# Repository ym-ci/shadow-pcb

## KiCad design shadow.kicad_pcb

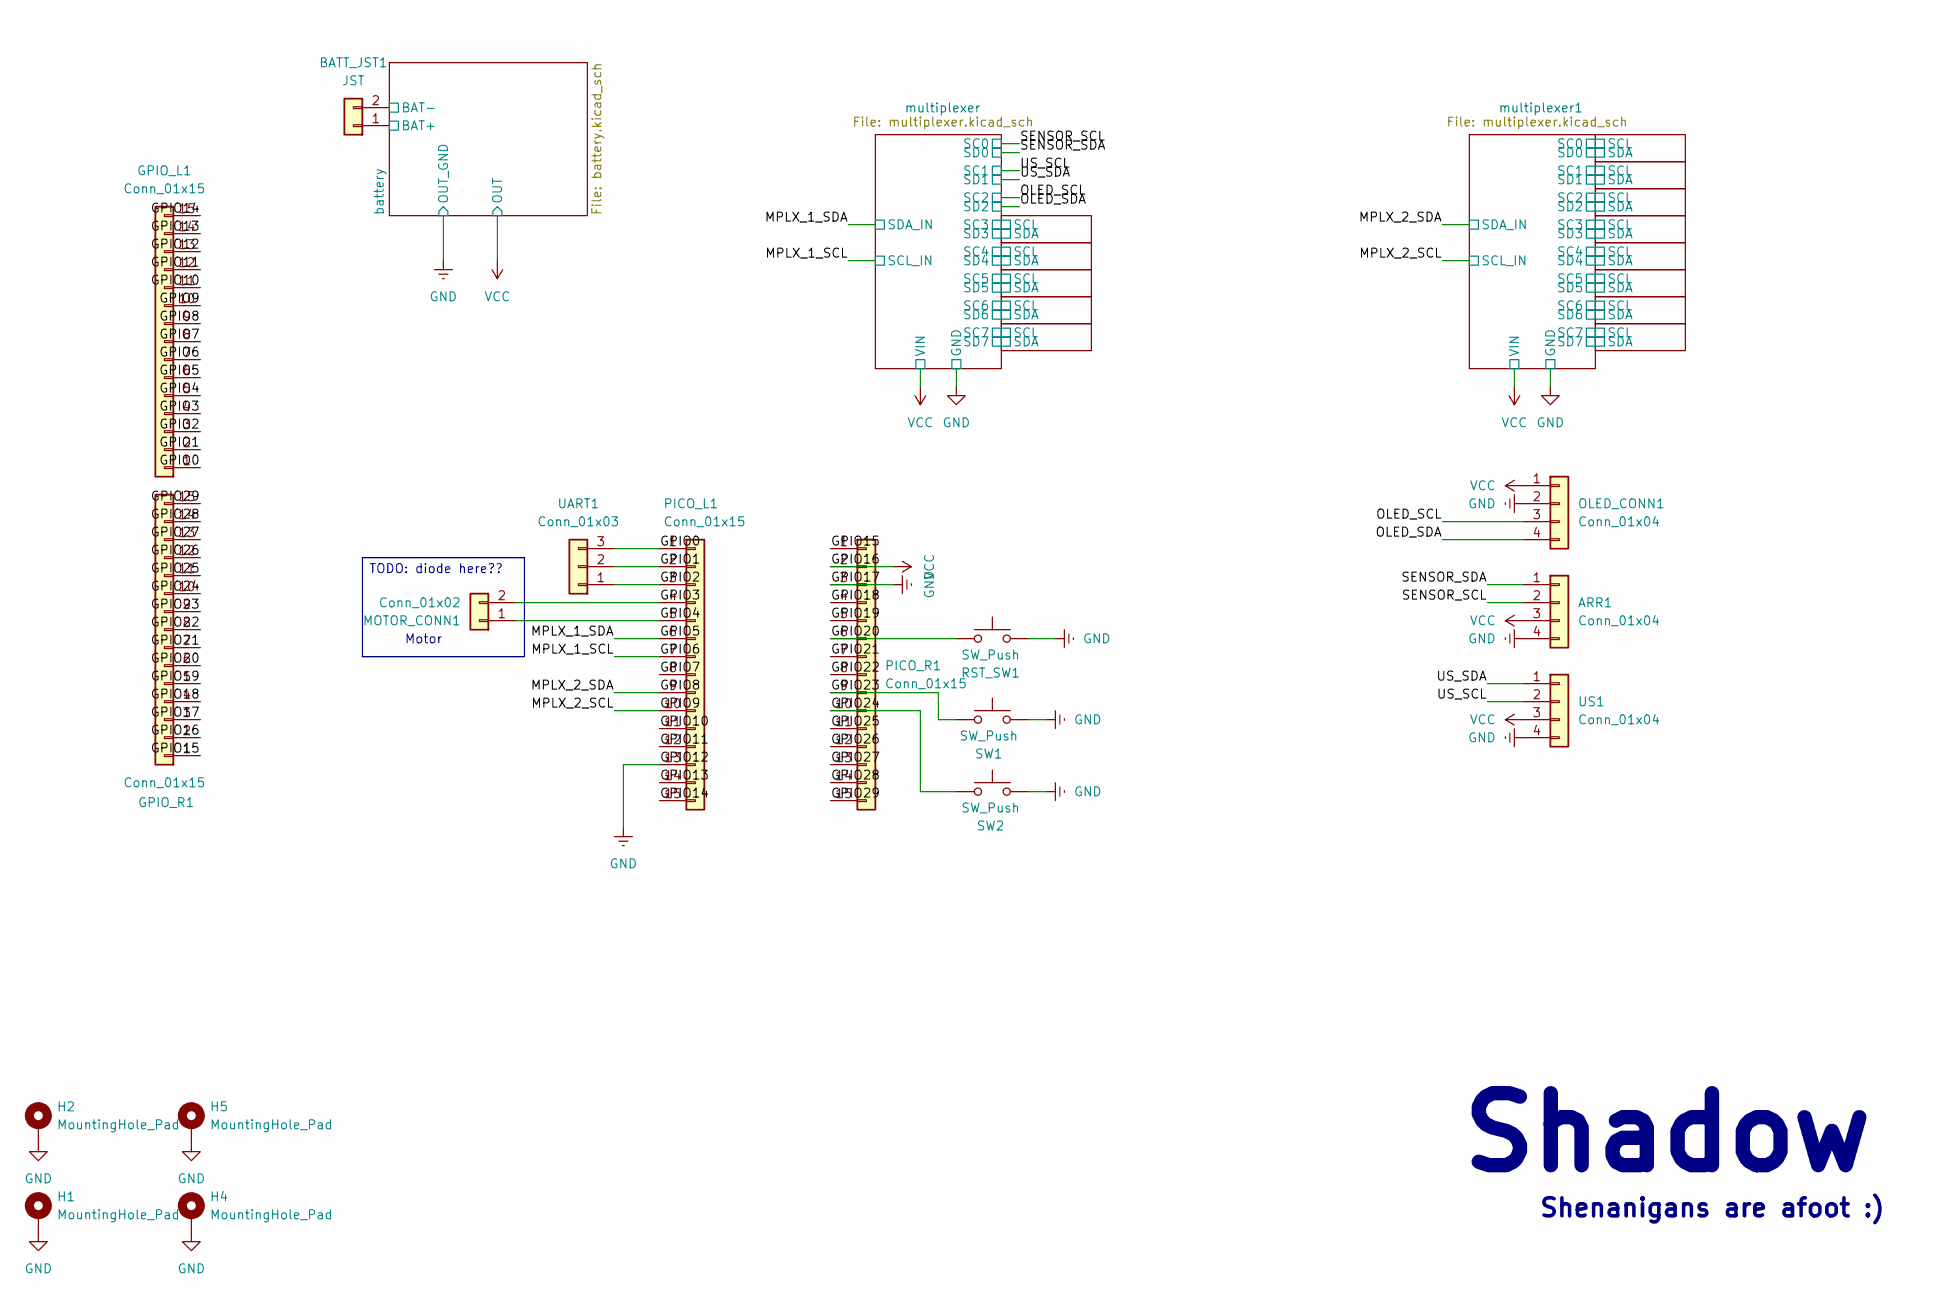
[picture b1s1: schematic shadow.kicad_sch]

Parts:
ARR1: Conn_01x04; PinSocket_1x04_P2.54mm_Vertical
BATT_JST1: JST; JST_XH_B2B-XH-A_1x02_P2.50mm_Vertical
GPIO_L1: Conn_01x15; PinSocket_1x15_P2.54mm_Vertical
GPIO_R1: Conn_01x15; PinSocket_1x15_P2.54mm_Vertical
H1, H2, H4, H5: MountingHole_Pad; MountingHole_4.3mm_M4_DIN965_Pad
MOTOR_CONN1: Conn_01x02; PinSocket_1x02_P2.54mm_Vertical
OLED_CONN1: Conn_01x04; PinSocket_1x04_P2.54mm_Vertical
PICO_L1: Conn_01x15; PinSocket_1x15_P2.54mm_Vertical
PICO_R1: Conn_01x15; PinSocket_1x15_P2.54mm_Vertical
RST_SW1: SW_Push; SW_PUSH_6mm
SW1, SW2: SW_Push; SW_PUSH_6mm
UART1: Conn_01x03; PinSocket_1x03_P2.54mm_Vertical
US1: Conn_01x04; PinSocket_1x04_P2.54mm_Vertical

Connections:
/GPIO0: GPIO_L1.1, PICO_L1.1, UART1.3
/GPIO1: GPIO_L1.2, PICO_L1.2, UART1.2
/GPIO2: GPIO_L1.3, PICO_L1.3, UART1.1
/GPIO3: GPIO_L1.4, MOTOR_CONN1.2, PICO_L1.4
/GPIO4: GPIO_L1.5, MOTOR_CONN1.1, PICO_L1.5
/GPIO5: GPIO_L1.6, PICO_L1.6; also elsewhere on the board
/GPIO6: GPIO_L1.7, PICO_L1.7; also elsewhere on the board
/GPIO7: GPIO_L1.8, PICO_L1.8
/GPIO8: GPIO_L1.9, PICO_L1.9; also elsewhere on the board
/GPIO9: GPIO_L1.10, PICO_L1.10; also elsewhere on the board
/GPIO10: GPIO_L1.11, PICO_L1.11
/GPIO11: GPIO_L1.12, PICO_L1.12
/GPIO13: GPIO_L1.14, PICO_L1.14
/GPIO14: GPIO_L1.15, PICO_L1.15
/GPIO15: GPIO_R1.1, PICO_R1.1
/GPIO18: GPIO_R1.4, PICO_R1.4
/GPIO19: GPIO_R1.5, PICO_R1.5
/GPIO20: GPIO_R1.6, PICO_R1.6, RST_SW1.1
/GPIO21: GPIO_R1.7, PICO_R1.7
/GPIO22: GPIO_R1.8, PICO_R1.8
/GPIO23: GPIO_R1.9, PICO_R1.9, SW1.1
/GPIO24: GPIO_R1.10, PICO_R1.10, SW2.1
/GPIO25: GPIO_R1.11, PICO_R1.11
/GPIO26: GPIO_R1.12, PICO_R1.12
/GPIO27: GPIO_R1.13, PICO_R1.13
/GPIO28: GPIO_R1.14, PICO_R1.14
/GPIO29: GPIO_R1.15, PICO_R1.15
/OLED_SCL: OLED_CONN1.3; also elsewhere on the board
/OLED_SDA: OLED_CONN1.4; also elsewhere on the board
/SENSOR_SCL: ARR1.2; also elsewhere on the board
/SENSOR_SDA: ARR1.1; also elsewhere on the board
/US_SCL: US1.2; also elsewhere on the board
/US_SDA: US1.1; also elsewhere on the board
/battery/BAT+: BATT_JST1.1; also elsewhere on the board
/battery/BAT-: BATT_JST1.2; also elsewhere on the board
GND: ARR1.4, GPIO_L1.13, GPIO_R1.3, H1.1, H2.1, H4.1, H5.1, OLED_CONN1.2, PICO_L1.13, PICO_R1.3, RST_SW1.2, SW1.2, SW2.2, US1.4; also elsewhere on the board
VCC: ARR1.3, GPIO_R1.2, OLED_CONN1.1, PICO_R1.2, US1.3; also elsewhere on the board

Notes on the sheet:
TODO: diode here??
Shadow
Motor
Shenanigans are afoot :)

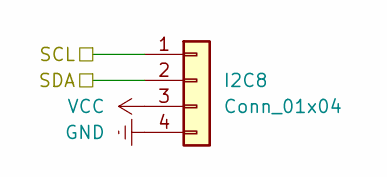
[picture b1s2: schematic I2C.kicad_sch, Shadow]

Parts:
I2C8: Conn_01x04; PinSocket_1x04_P2.54mm_Vertical

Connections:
/I2C8/SCL: I2C8.1; also elsewhere on the board
/I2C8/SDA: I2C8.2; also elsewhere on the board
GND: I2C8.4; also elsewhere on the board
VCC: I2C8.3; also elsewhere on the board

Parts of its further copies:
I2C0, I2C1, I2C2, I2C3, I2C4, I2C5, I2C6, I2C7, I2C9, I2C10, I2C11, I2C12: Conn_01x04; PinSocket_1x04_P2.54mm_Vertical

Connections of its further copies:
/I2C1/SCL: I2C1.1; also elsewhere on the board
/I2C1/SDA: I2C1.2; also elsewhere on the board
/I2C2/SCL: I2C2.1; also elsewhere on the board
/I2C2/SDA: I2C2.2; also elsewhere on the board
/I2C3/SCL: I2C3.1; also elsewhere on the board
/I2C3/SDA: I2C3.2; also elsewhere on the board
/I2C4/SCL: I2C4.1; also elsewhere on the board
/I2C4/SDA: I2C4.2; also elsewhere on the board
/I2C5/SCL: I2C5.1; also elsewhere on the board
/I2C5/SDA: I2C5.2; also elsewhere on the board
/I2C6/SCL: I2C6.1; also elsewhere on the board
/I2C6/SDA: I2C6.2; also elsewhere on the board
/I2C7/SCL: I2C7.1; also elsewhere on the board
/I2C7/SDA: I2C7.2; also elsewhere on the board
/I2C9/SCL: I2C9.1; also elsewhere on the board
/I2C9/SDA: I2C9.2; also elsewhere on the board
/I2C10/SCL: I2C10.1; also elsewhere on the board
/I2C10/SDA: I2C10.2; also elsewhere on the board
/I2C11/SCL: I2C11.1; also elsewhere on the board
/I2C11/SDA: I2C11.2; also elsewhere on the board
/I2C12/SCL: I2C12.1; also elsewhere on the board
/I2C12/SDA: I2C12.2; also elsewhere on the board
/I2C/SCL: I2C0.1; also elsewhere on the board
/I2C/SDA: I2C0.2; also elsewhere on the board
GND: I2C0.4, I2C1.4, I2C2.4, I2C3.4, I2C4.4, I2C5.4, I2C6.4, I2C7.4, I2C9.4, I2C10.4, I2C11.4, I2C12.4; also elsewhere on the board
VCC: I2C0.3, I2C1.3, I2C2.3, I2C3.3, I2C4.3, I2C5.3, I2C6.3, I2C7.3, I2C9.3, I2C10.3, I2C11.3, I2C12.3; also elsewhere on the board

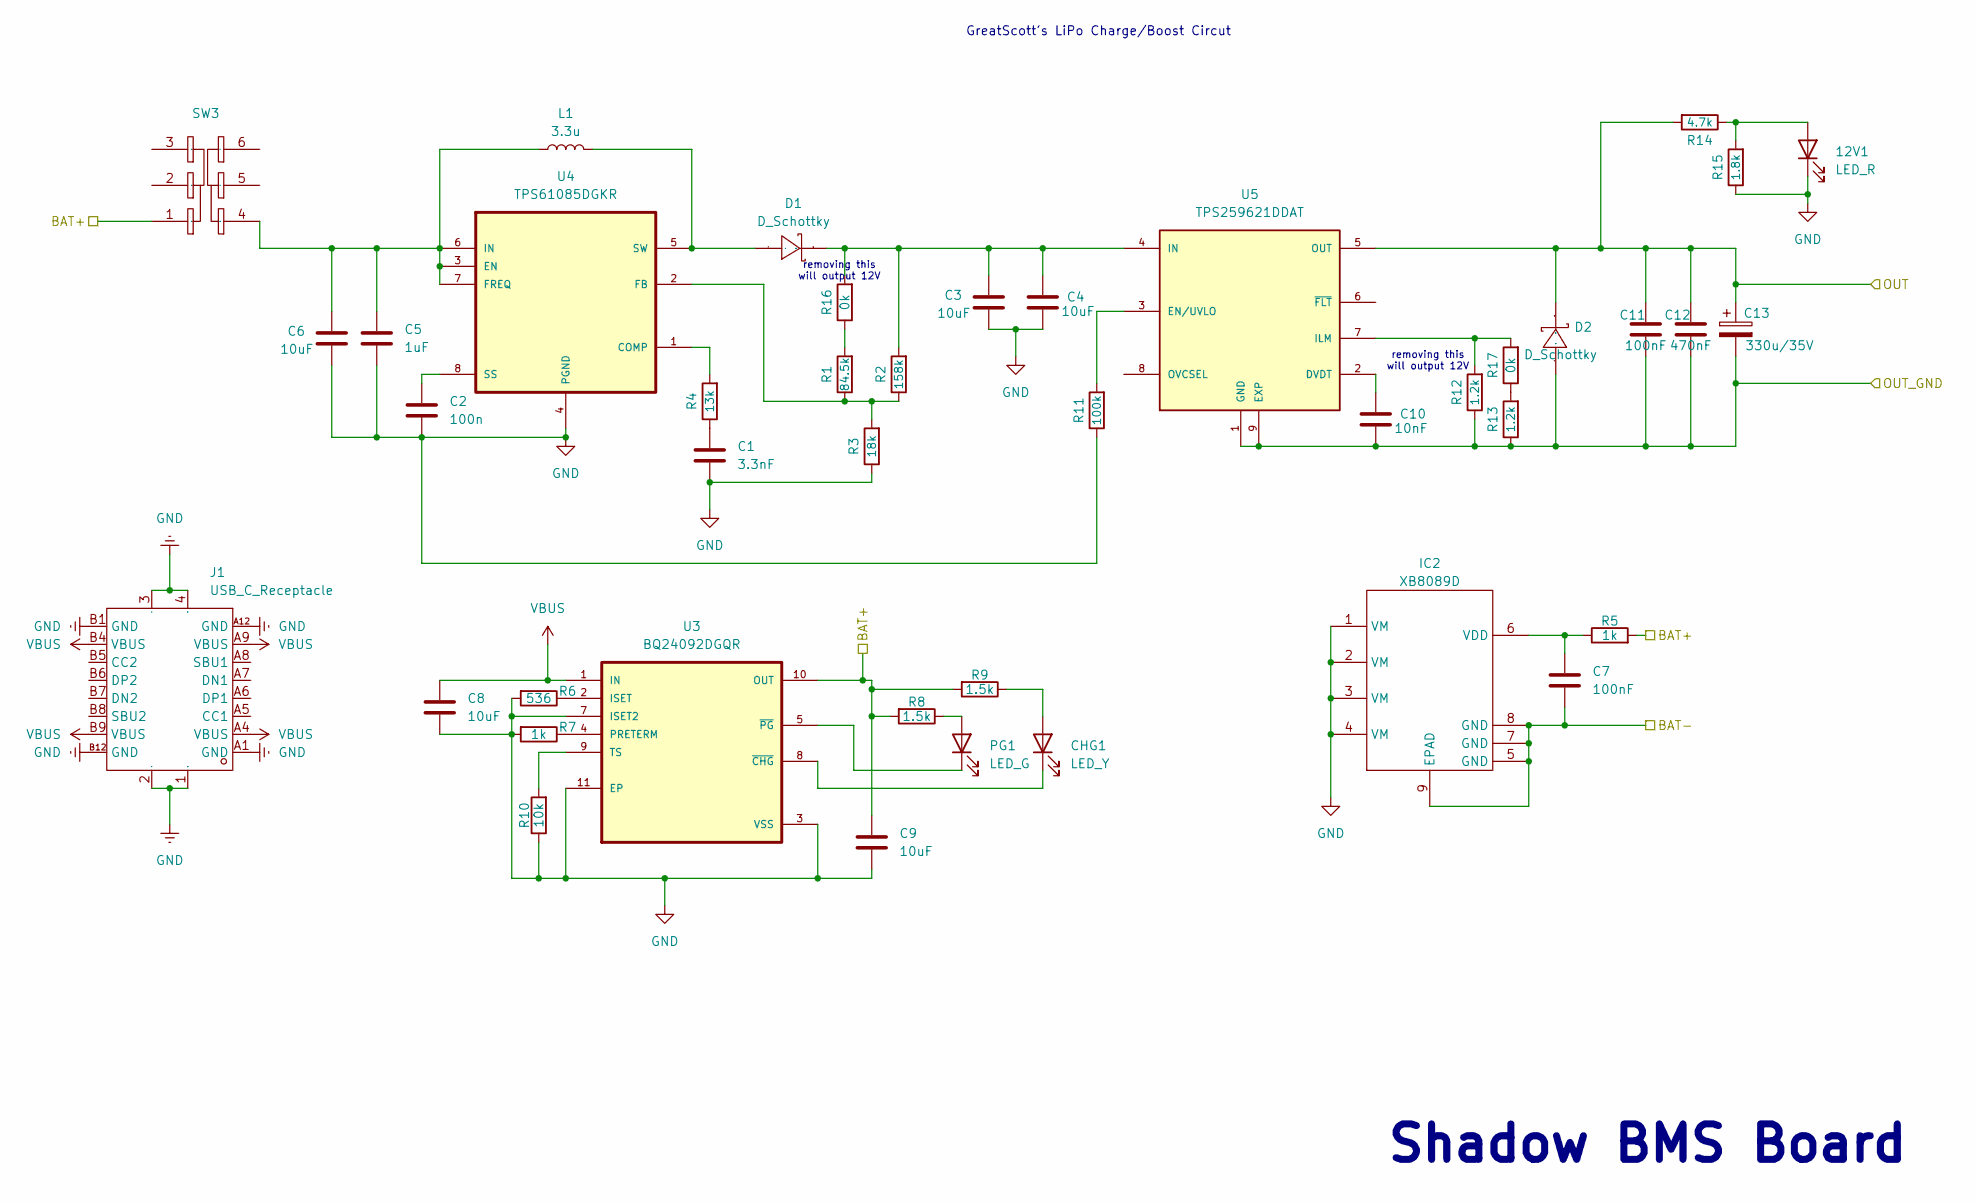
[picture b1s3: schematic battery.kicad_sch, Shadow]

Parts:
12V1: LED_R; LED_0603_1608Metric
C1: 3.3nF; C_0603_1608Metric
C2: 100n; C_1206_3216Metric
C3, C4, C6, C8, C9: 10uF; C_1206_3216Metric
C5: 1uF; C_1206_3216Metric
C7, C11: 100nF; C_1206_3216Metric
C10: 10nF; C_1206_3216Metric
C12: 470nF; C_1206_3216Metric
C13: 330u/35V; CP_Radial_D10.0mm_P5.00mm
CHG1: LED_Y; LED_0805_2012Metric
D1, D2: D_Schottky; SMA_L4.2-W2.6-LS5.3-RD; Manufacturer Part SS14; LCSC Part Name 电压:40V 电流:1A
IC2: XB8089D; Manufacturer Part XB8089D; LCSC Part Name XB8089D
J1: USB_C_Receptacle; TYPE-C-SMD_20009-UCAF001-X; Manufacturer Part TYPE-C 16PIN L8.35; LCSC Part Name Type-C 母 卧贴
L1: 3.3u; L_7.3x7.3_H4.5
PG1: LED_G; LED_0805_2012Metric
R1: 84.5k; R_1206_3216Metric
R2: 158k; R_1206_3216Metric
R3: 18k; R_0603_1608Metric
R4: 13k; R_0603_1608Metric
R5, R7: 1k; R_1206_3216Metric
R6: 536; R_1206_3216Metric
R8, R9: 1.5k; R_0805_2012Metric
R10: 10k; R_1206_3216Metric
R11: 100k; R_1206_3216Metric
R12, R13: 1.2k; R_0805_2012Metric
R14: 4.7k; R_1206_3216Metric
R15: 1.8k; R_0603_1608Metric
R16, R17: 0k; R_1206_3216Metric
SW3: SW-TH_K3-2235D-F1; Manufacturer Part K3-2235D-F1; LCSC Part Name 直插双档 滑动开关
U3: BQ24092DGQR; IC_XTR111AIDGQR
U4: TPS61085DGKR; SOP65P490X110-8N
U5: TPS259621DDAT; IC_TPS259621DDAT; PARTREV A

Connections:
/battery/BAT+: C9.1, R5.2, R8.2, R9.2, SW3.1, U3.10 (OUT); also elsewhere on the board
/battery/BAT-: C7.2, IC2.5 (GND), IC2.7 (GND), IC2.8 (GND), IC2.9 (EPAD); also elsewhere on the board
GND: 12V1.1 (K), C1.2, C2.2, C3.2, C4.2, C5.2, C6.2, C8.2, C9.2, C10.2, C11.2, C12.2, C13.2, D2.2 (A), IC2.1 (VM), IC2.2 (VM), IC2.3 (VM), IC2.4 (VM), J1.1, J1.2, J1.3, J1.4, J1.A1 (GND), J1.A12 (GND), J1.B1 (GND), J1.B12 (GND), R3.1, R6.2, R7.2, R10.1, R11.1, R12.1, R13.1, R15.1, U3.3 (VSS), U3.7 (ISET2), U3.11 (EP), U4.4 (PGND), U5.1 (GND), U5.9 (EXP); also elsewhere on the board
unnamed: 12V1.2 (A), R14.1, R15.2
unnamed: C1.1, R4.1
unnamed: CHG1.2 (A), R9.1
unnamed: CHG1.1 (K), U3.8 (~CHG)
unnamed: D1.2 (A), L1.2, U4.5 (SW)
unnamed: C3.1, C4.1, D1.1 (K), R2.2, R16.2, U5.4 (IN)
unnamed: C7.1, IC2.6 (VDD), R5.1
unnamed: PG1.2 (A), R8.1
unnamed: PG1.1 (K), U3.5 (~PG)
unnamed: R1.2, R16.1
unnamed: R13.2, R17.1
unnamed: R6.1, U3.2 (ISET)
unnamed: R7.1, U3.4 (PRETERM)
unnamed: R10.2, U3.9 (TS)
unnamed: R4.2, U4.1 (COMP)
unnamed: C5.1, C6.1, L1.1, SW3.4, U4.3 (EN), U4.6 (IN), U4.7 (FREQ)
unnamed: R1.1, R2.1, R3.2, U4.2 (FB)
unnamed: C2.1, U4.8 (SS)
unnamed: C10.1, U5.2 (DVDT)
unnamed: R11.2, U5.3 (EN/UVLO)
unnamed: R12.2, R17.2, U5.7 (ILM)
VBUS: C8.1, J1.A4 (VBUS), J1.A9 (VBUS), J1.B4 (VBUS), J1.B9 (VBUS), U3.1 (IN)
VCC: C11.1, C12.1, C13.1, D2.1 (K), R14.2, U5.5 (OUT); also elsewhere on the board

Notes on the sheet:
GreatScott's LiPo Charge/Boost Circut
Shadow BMS Board
removing this will output 12V

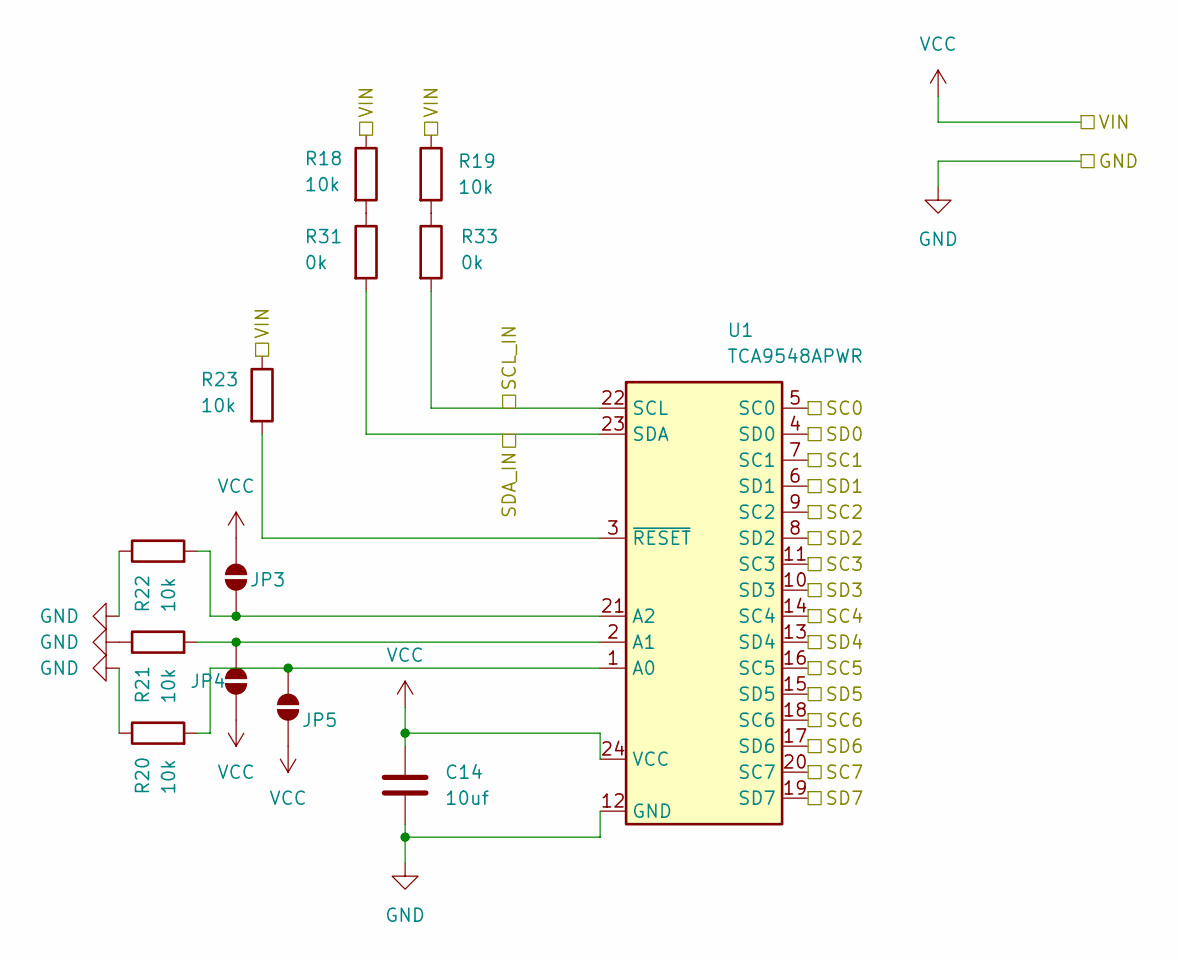
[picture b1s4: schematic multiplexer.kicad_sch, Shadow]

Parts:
C14: 10uf; C_1206_3216Metric
JP3, JP4, JP5: SolderJumper_2_Open; SolderJumper-2_P1.3mm_Open_Pad1.0x1.5mm
R18, R19, R20, R21, R22, R23: 10k; R_1206_3216Metric
R31, R33: 0k; R_1206_3216Metric
U1: TCA9548APWR; TSSOP-24_4.4x7.8mm_P0.65mm

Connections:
/GPIO5: R31.2, U1.23 (SDA); also elsewhere on the board
/GPIO6: R33.2, U1.22 (SCL); also elsewhere on the board
/I2C8/SCL: U1.11 (SC3); also elsewhere on the board
/I2C8/SDA: U1.10 (SD3); also elsewhere on the board
/I2C9/SCL: U1.14 (SC4); also elsewhere on the board
/I2C9/SDA: U1.13 (SD4); also elsewhere on the board
/I2C10/SCL: U1.16 (SC5); also elsewhere on the board
/I2C10/SDA: U1.15 (SD5); also elsewhere on the board
/I2C11/SCL: U1.18 (SC6); also elsewhere on the board
/I2C11/SDA: U1.17 (SD6); also elsewhere on the board
/I2C12/SCL: U1.20 (SC7); also elsewhere on the board
/I2C12/SDA: U1.19 (SD7); also elsewhere on the board
/OLED_SCL: U1.9 (SC2); also elsewhere on the board
/OLED_SDA: U1.8 (SD2); also elsewhere on the board
/SENSOR_SCL: U1.5 (SC0); also elsewhere on the board
/SENSOR_SDA: U1.4 (SD0); also elsewhere on the board
/US_SCL: U1.7 (SC1); also elsewhere on the board
/US_SDA: U1.6 (SD1); also elsewhere on the board
GND: C14.2, R20.1, R21.1, R22.1, U1.12 (GND); also elsewhere on the board
unnamed: JP3.1 (A), R22.2, U1.21 (A2)
unnamed: JP4.2 (B), R21.2, U1.2 (A1)
unnamed: JP5.2 (B), R20.2, U1.1 (A0)
unnamed: R18.2, R31.1
unnamed: R19.2, R33.1
unnamed: R23.2, U1.3 (~RESET)
VCC: C14.1, JP3.2 (B), JP4.1 (A), JP5.1 (A), R18.1, R19.1, R23.1, U1.24 (VCC); also elsewhere on the board

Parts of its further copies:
C15: 10uf; C_1206_3216Metric
JP6, JP7, JP8: SolderJumper_2_Open; SolderJumper-2_P1.3mm_Open_Pad1.0x1.5mm
R24, R25, R26, R27, R28, R29: 10k; R_1206_3216Metric
R32, R34: 0k; R_1206_3216Metric
U2: TCA9548APWR; TSSOP-24_4.4x7.8mm_P0.65mm

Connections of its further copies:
/GPIO8: R32.2, U2.23 (SDA); also elsewhere on the board
/GPIO9: R34.2, U2.22 (SCL); also elsewhere on the board
/I2C1/SCL: U2.7 (SC1); also elsewhere on the board
/I2C1/SDA: U2.6 (SD1); also elsewhere on the board
/I2C2/SCL: U2.9 (SC2); also elsewhere on the board
/I2C2/SDA: U2.8 (SD2); also elsewhere on the board
/I2C3/SCL: U2.11 (SC3); also elsewhere on the board
/I2C3/SDA: U2.10 (SD3); also elsewhere on the board
/I2C4/SCL: U2.14 (SC4); also elsewhere on the board
/I2C4/SDA: U2.13 (SD4); also elsewhere on the board
/I2C5/SCL: U2.16 (SC5); also elsewhere on the board
/I2C5/SDA: U2.15 (SD5); also elsewhere on the board
/I2C6/SCL: U2.18 (SC6); also elsewhere on the board
/I2C6/SDA: U2.17 (SD6); also elsewhere on the board
/I2C7/SCL: U2.20 (SC7); also elsewhere on the board
/I2C7/SDA: U2.19 (SD7); also elsewhere on the board
/I2C/SCL: U2.5 (SC0); also elsewhere on the board
/I2C/SDA: U2.4 (SD0); also elsewhere on the board
GND: C15.2, R24.1, R25.1, R29.1, U2.12 (GND); also elsewhere on the board
unnamed: JP6.1 (A), R29.2, U2.21 (A2)
unnamed: JP7.2 (B), R24.2, U2.2 (A1)
unnamed: JP8.2 (B), R25.2, U2.1 (A0)
unnamed: R27.2, R32.1
unnamed: R28.2, R34.1
unnamed: R26.2, U2.3 (~RESET)
VCC: C15.1, JP6.2 (B), JP7.1 (A), JP8.1 (A), R26.1, R27.1, R28.1, U2.24 (VCC); also elsewhere on the board

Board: 2 copper layers, 98 parts (6 on the bottom side), 97 nets, no tracks yet.

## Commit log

2025-01-05 feat: finish up control circut
2025-01-05 chore: stop tracking workspace-specific files
2025-01-05 finish circut
2025-01-05 chore: replace sensors with labels
2025-01-05 feat: ground usb shield via 0k resistor
2025-01-06 start work on i2c multiplexer
2025-01-25 FINISH SCHEMATICS
2025-01-25 aaaa
2025-01-25 assign footprints
2025-01-25 start work on pcb design
2025-01-25 switch to new (better) lipo charger design
2025-01-25 Add new lipo charger to pcb
2025-01-25 a lot of work on pcb
2025-01-25 finish pcb layout
2025-01-25 make pcb smaller
2025-01-25 more work on pcb
2025-01-25 add mounting holes
2025-01-25 ground mounting holes
2025-01-25 route pcb
2025-01-26 pick out some parts from jlc
2025-01-26 Update to new cap footprint
2025-01-26 route traces
2025-01-26 fix pico mount width and orientation of left gpio
2025-01-26 fix some stuff and retrace
2025-01-26 v0.0.1
2025-01-26 finish pcb
2025-01-26 finalize production files + pcbway
2025-01-26 move all backside components to front and make it work for jlc basic components
